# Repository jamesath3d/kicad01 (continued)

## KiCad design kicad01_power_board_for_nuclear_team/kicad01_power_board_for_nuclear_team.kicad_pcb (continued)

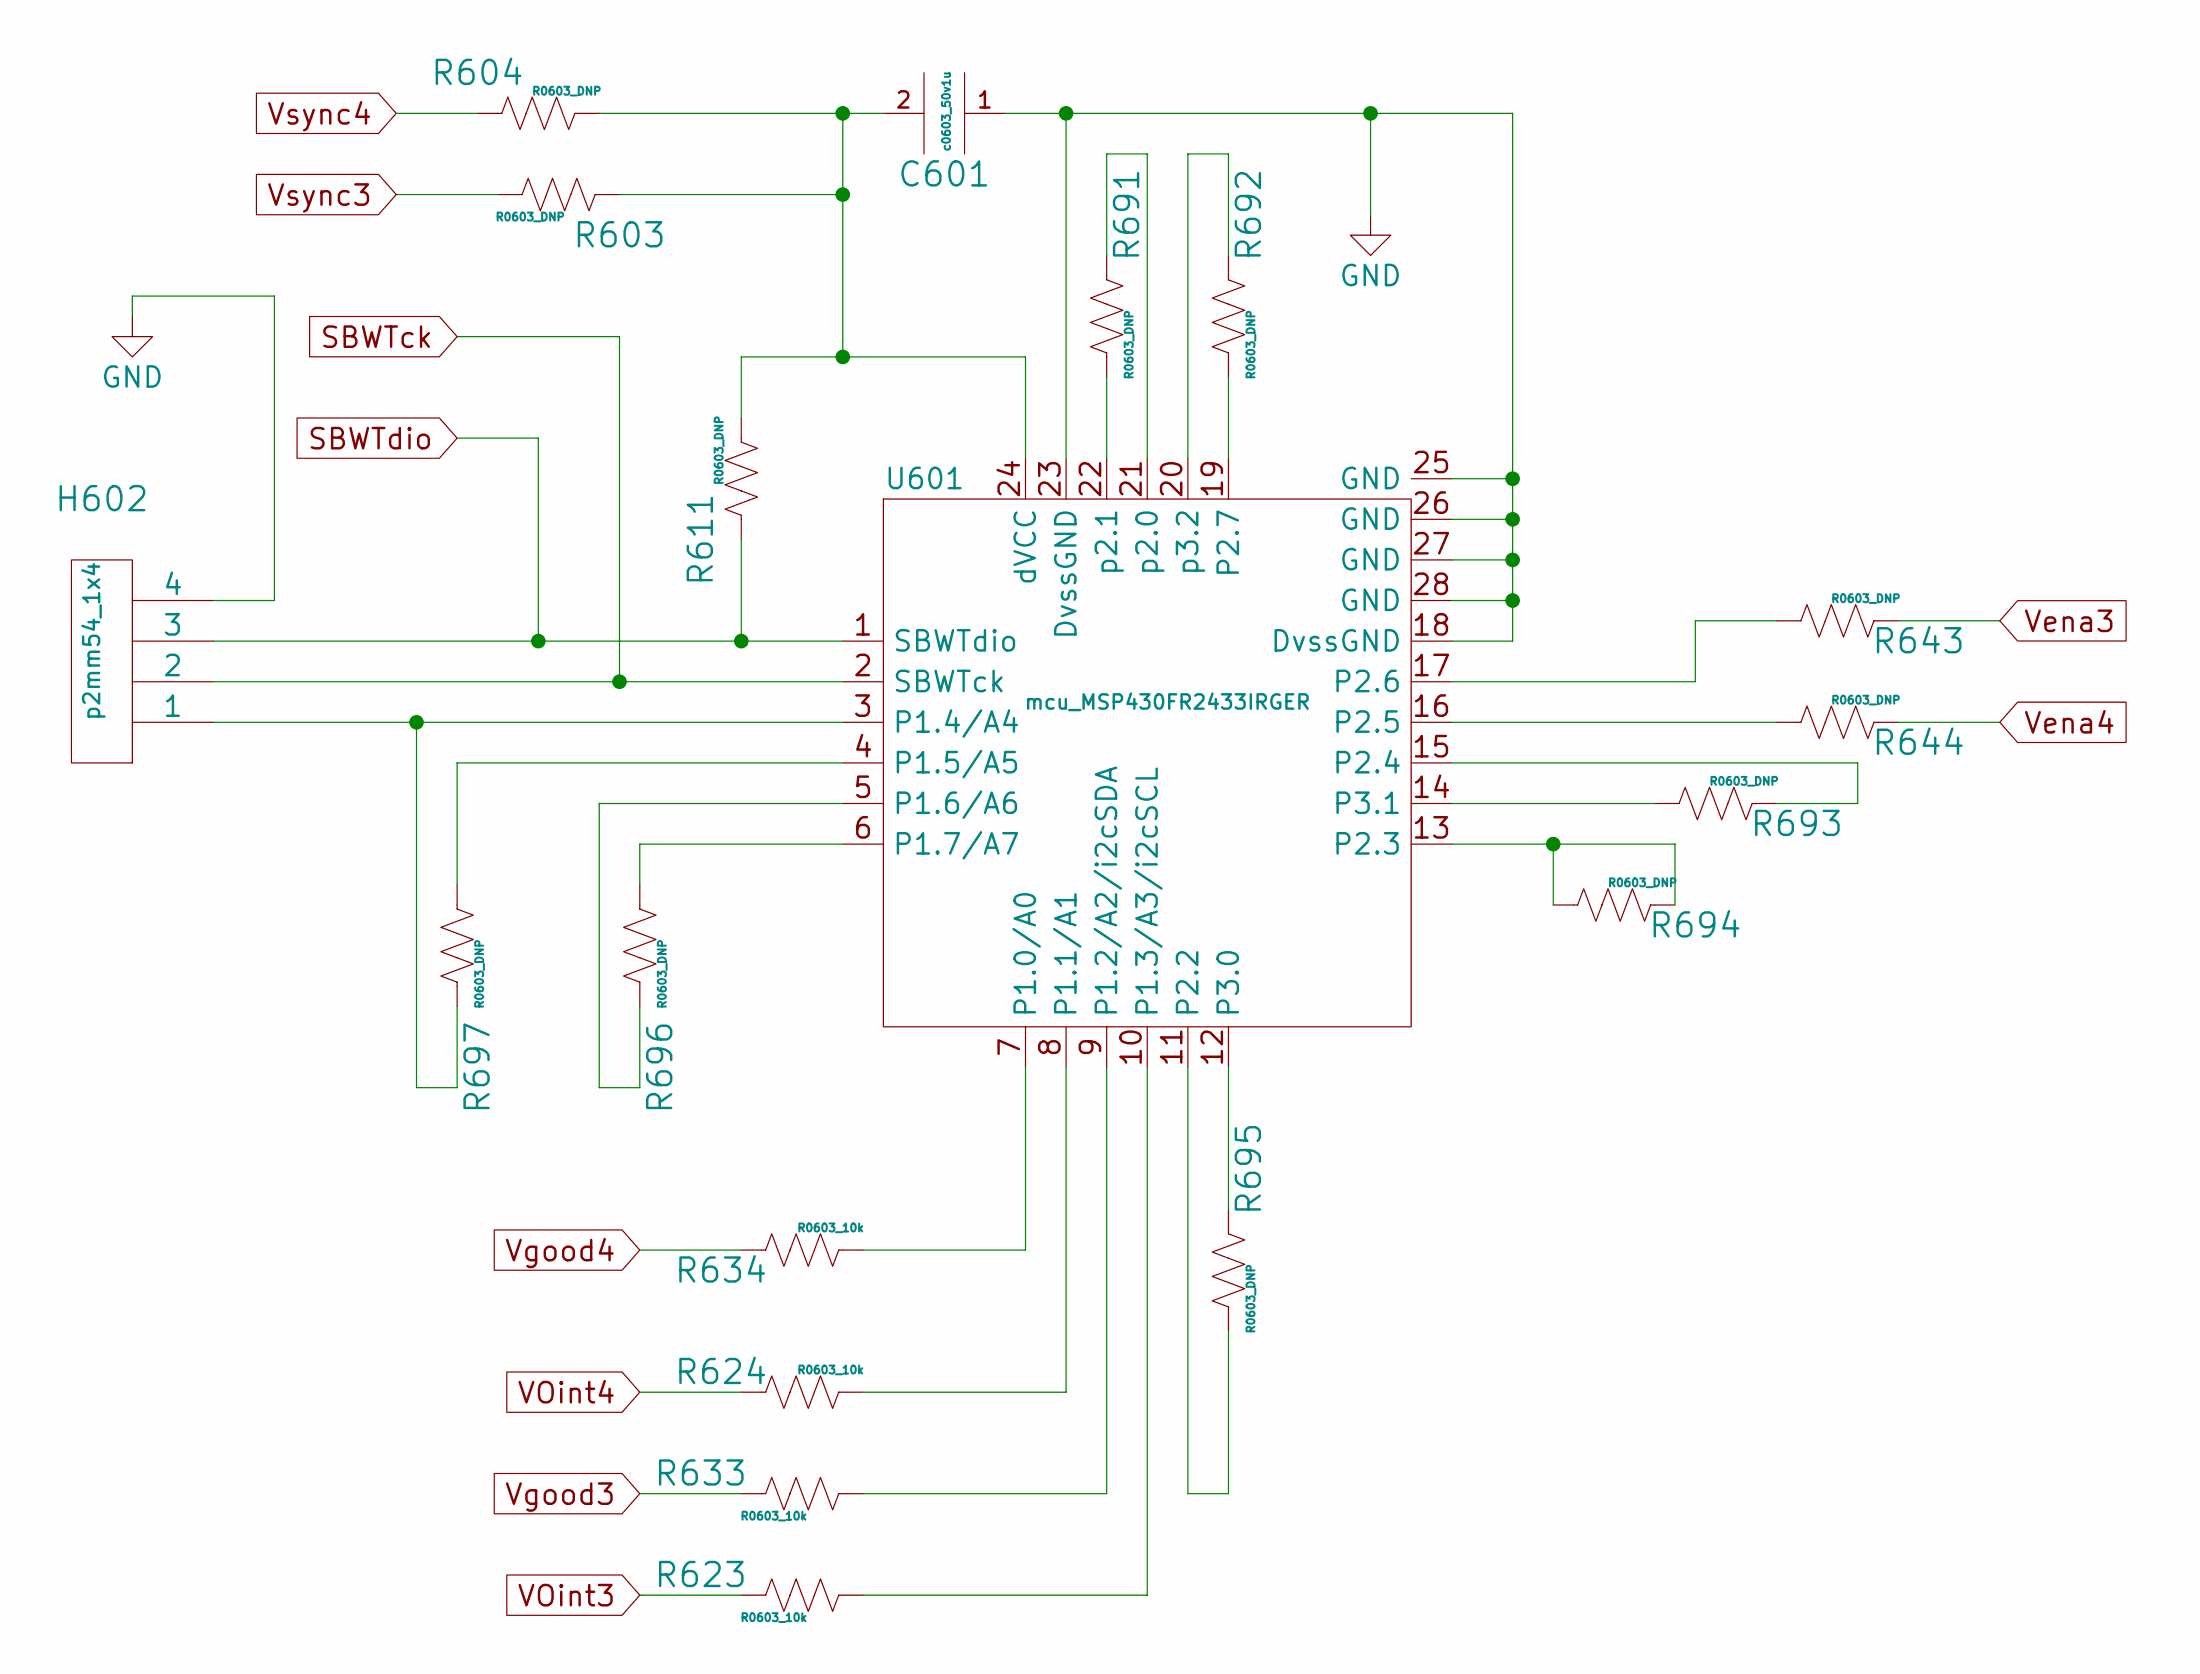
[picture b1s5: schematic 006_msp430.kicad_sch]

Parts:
C601: c0603_50v1u; C0603; PartNum C1608X5R1H105K080AB
H602: p2mm54_1x4; PartNum 3M156515-04-ND
R603, R604, R611, R643, R644, R691, R692, R693, R694, R695, R696, R697: R0603_DNP; R0603; PartNum R0603_DNP
R623, R624, R633, R634: R0603_10k; R0603; PartNum ERJ-PA3F1002V
U601: mcu_MSP430FR2433IRGER; QFN-24-1EP_4x4mm_P0.5mm_EP2.8x2.8mmX; PartNum MSP430FR2433IRGER

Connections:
GND: C601.1, H602.4, U601.18 (DvssGND), U601.23 (DvssGND), U601.25 (GND), U601.26 (GND), U601.27 (GND), U601.28 (GND); also elsewhere on the board
unnamed: C601.2, R603.2, R604.1, R611.1, U601.24 (dVCC)
unnamed: H602.1, R697.1, U601.3 (P1.4/A4)
unnamed: R623.2, U601.10 (P1.3/A3/i2cSCL)
unnamed: R624.1, U601.8 (P1.1/A1)
unnamed: R633.2, U601.9 (P1.2/A2/i2cSDA)
unnamed: R634.1, U601.7 (P1.0/A0)
unnamed: R643.2, U601.17 (P2.6)
unnamed: R644.2, U601.16 (P2.5)
unnamed: R691.1, U601.22 (p2.1)
unnamed: R691.2, U601.21 (p2.0)
unnamed: R692.1, U601.19 (P2.7)
unnamed: R692.2, U601.20 (p3.2)
unnamed: R693.1, U601.15 (P2.4)
unnamed: R693.2, U601.14 (P3.1)
unnamed: R694.1, R694.2, U601.13 (P2.3)
unnamed: R695.1, U601.11 (P2.2)
unnamed: R695.2, U601.12 (P3.0)
unnamed: R696.1, U601.5 (P1.6/A6)
unnamed: R696.2, U601.6 (P1.7/A7)
unnamed: R697.2, U601.4 (P1.5/A5)
SBWTck: H602.2, U601.2 (SBWTck)
SBWTdio: H602.3, R611.2, U601.1 (SBWTdio)
VOint3: R623.1; also elsewhere on the board
VOint4: R624.2; also elsewhere on the board
Vena3: R643.1; also elsewhere on the board
Vena4: R644.1; also elsewhere on the board
Vgood3: R633.1; also elsewhere on the board
Vgood4: R634.2; also elsewhere on the board
Vsync3: R603.1; also elsewhere on the board
Vsync4: R604.2; also elsewhere on the board

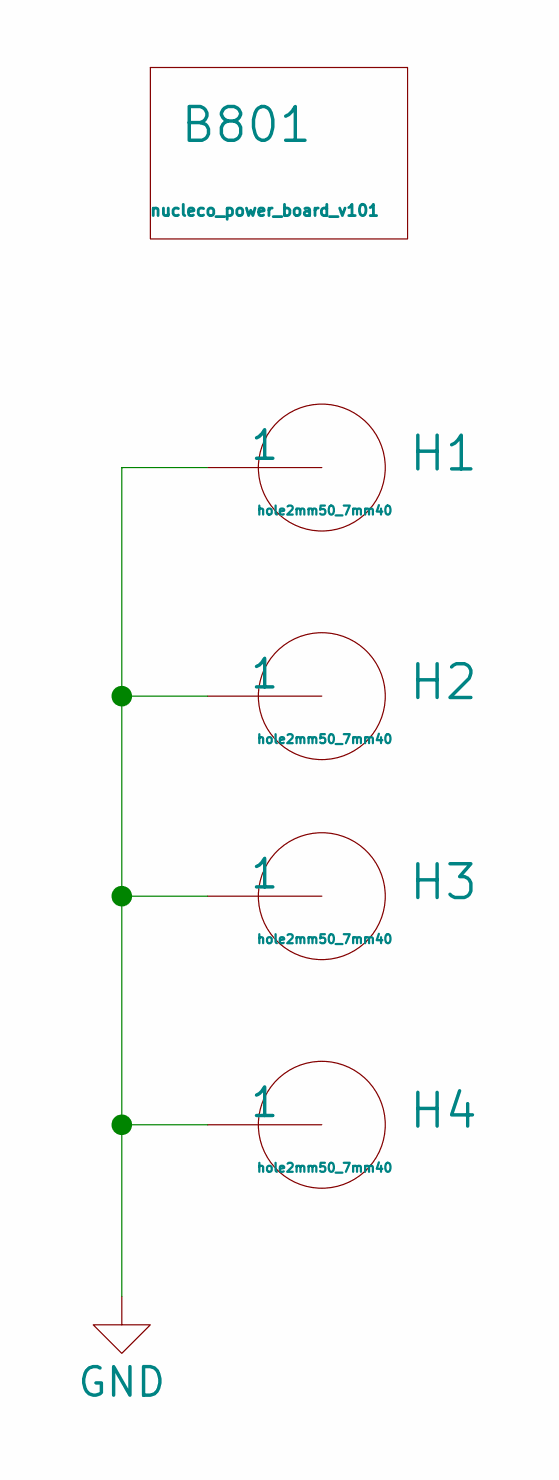
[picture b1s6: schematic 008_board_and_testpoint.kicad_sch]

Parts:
B801: nucleco_power_board_v101; PartNum DNP
H1, H2, H3, H4: hole2mm50_7mm40; PartNum hole2mm50_DNP

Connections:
GND: H1.1, H2.1, H3.1, H4.1; also elsewhere on the board

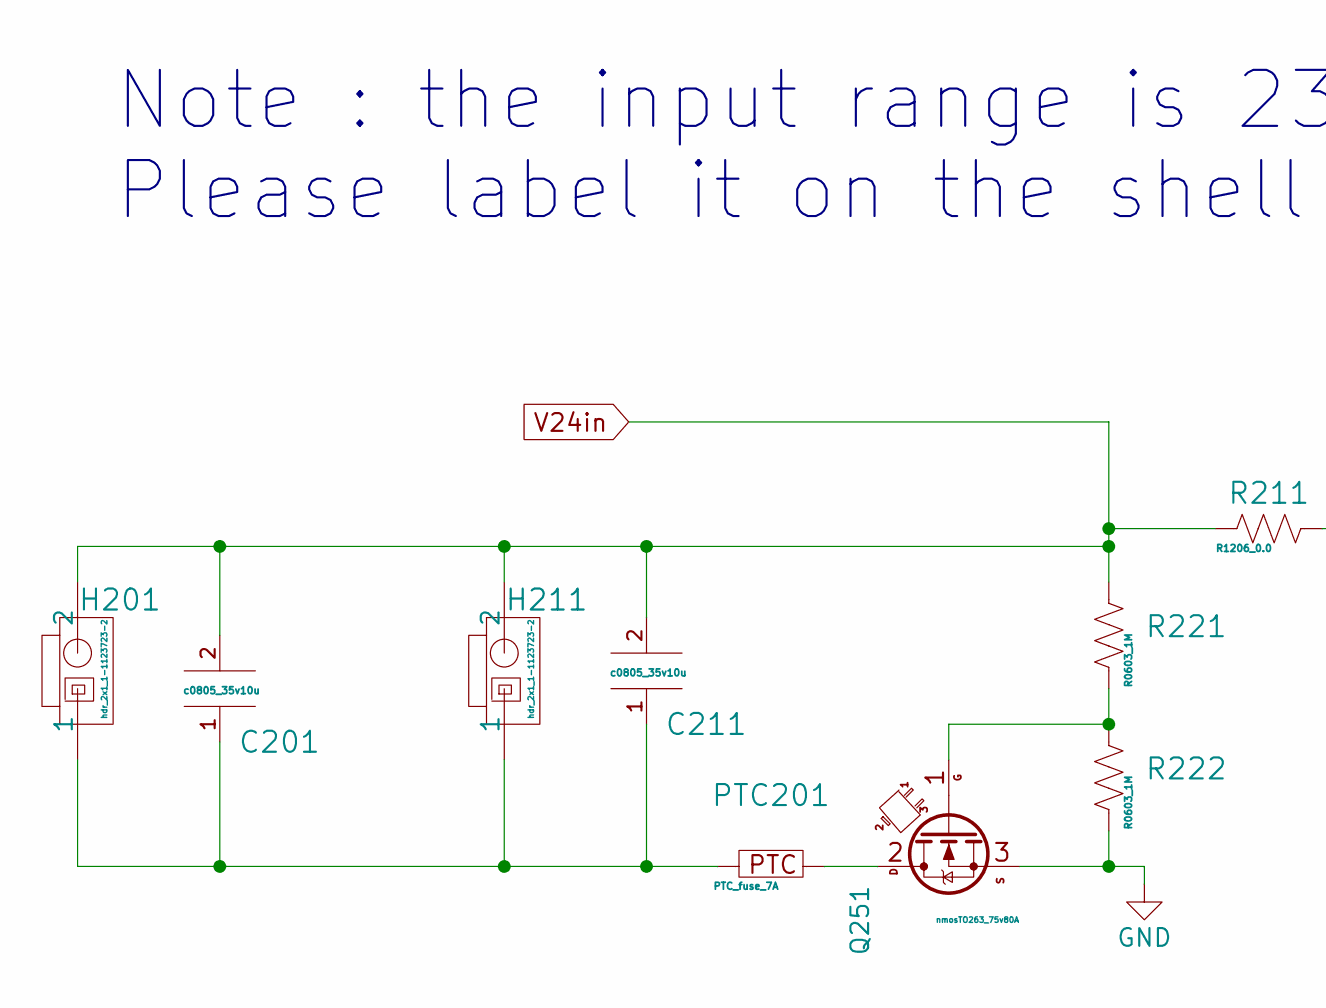
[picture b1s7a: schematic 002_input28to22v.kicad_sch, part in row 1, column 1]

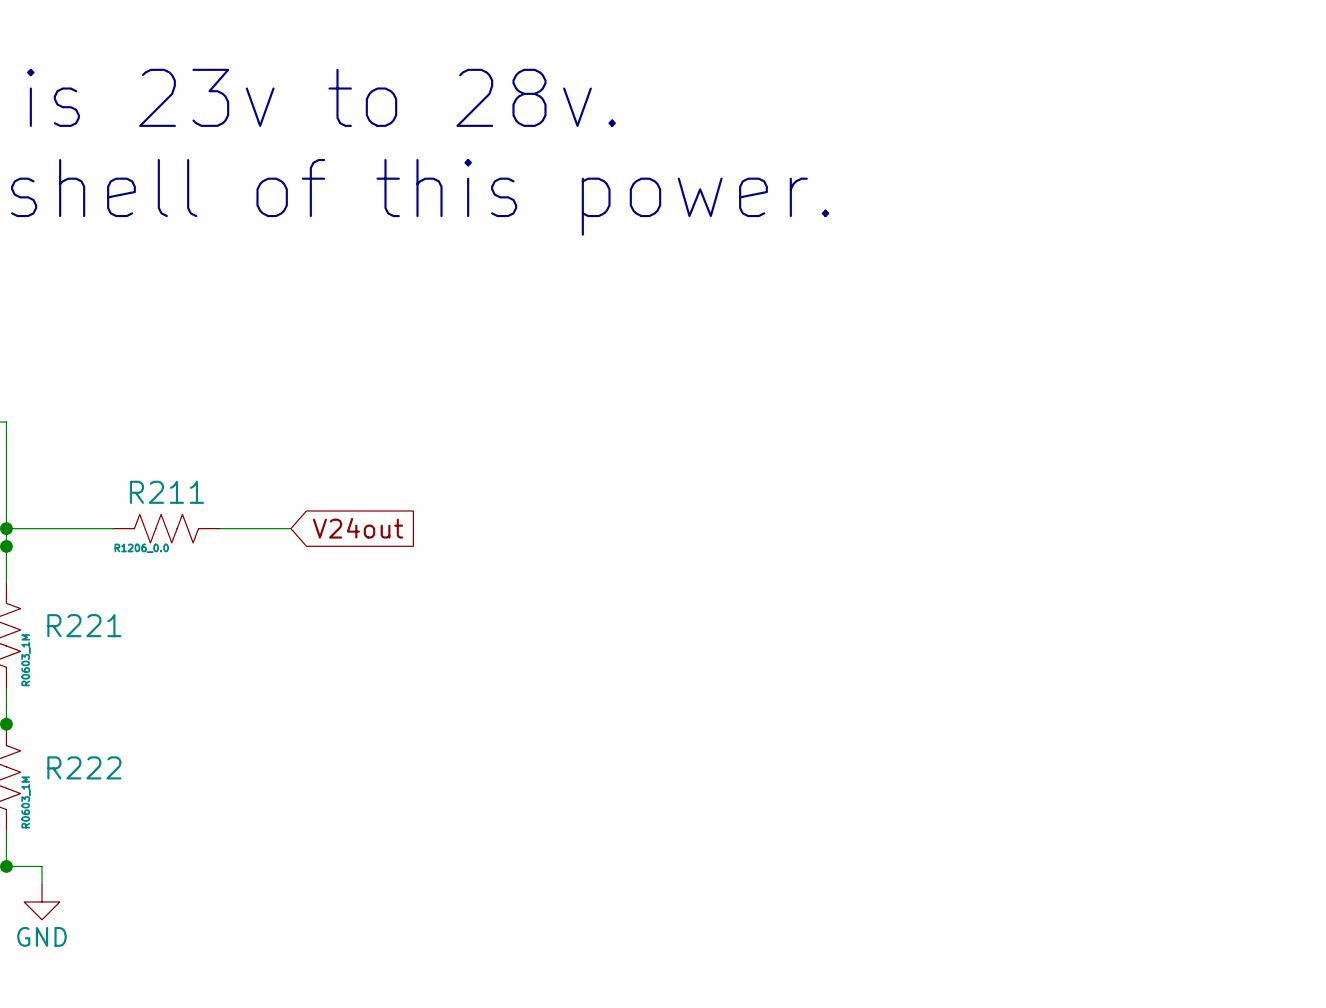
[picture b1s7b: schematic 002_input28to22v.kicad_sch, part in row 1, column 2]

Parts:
C201, C211: c0805_35v10u; C0805mix0603; PartNum C2012X5R1V106M085AC
H201, H211: hdr_2x1_1-1123723-2; PartNum 1-1123723-2
PTC201: PTC_fuse_7A; ptc_fuse_2920; PartNum 2920L700/12MR
Q251: nmosTO263_75v80A; d2pak_TO263; PartNum IRFS3607TRLPBF
R211: R1206_0.0; R1206mix0603; PartNum RC1206FR-070RL
R221, R222: R0603_1M; C0603; PartNum ERJ-U03F1004V

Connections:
GND: Q251.3 (S), R222.1; also elsewhere on the board
unnamed: C201.1, C211.1, H201.1, H211.1, PTC201.1
unnamed: PTC201.2, Q251.2 (D)
unnamed: Q251.1 (G), R221.1, R222.2
V24in: C201.2, C211.2, H201.2, H211.2, R211.1, R221.2; also elsewhere on the board
V24out: R211.2; also elsewhere on the board

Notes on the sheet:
Note : the input range is 23v to 28v. Please label it on the shell of this power.

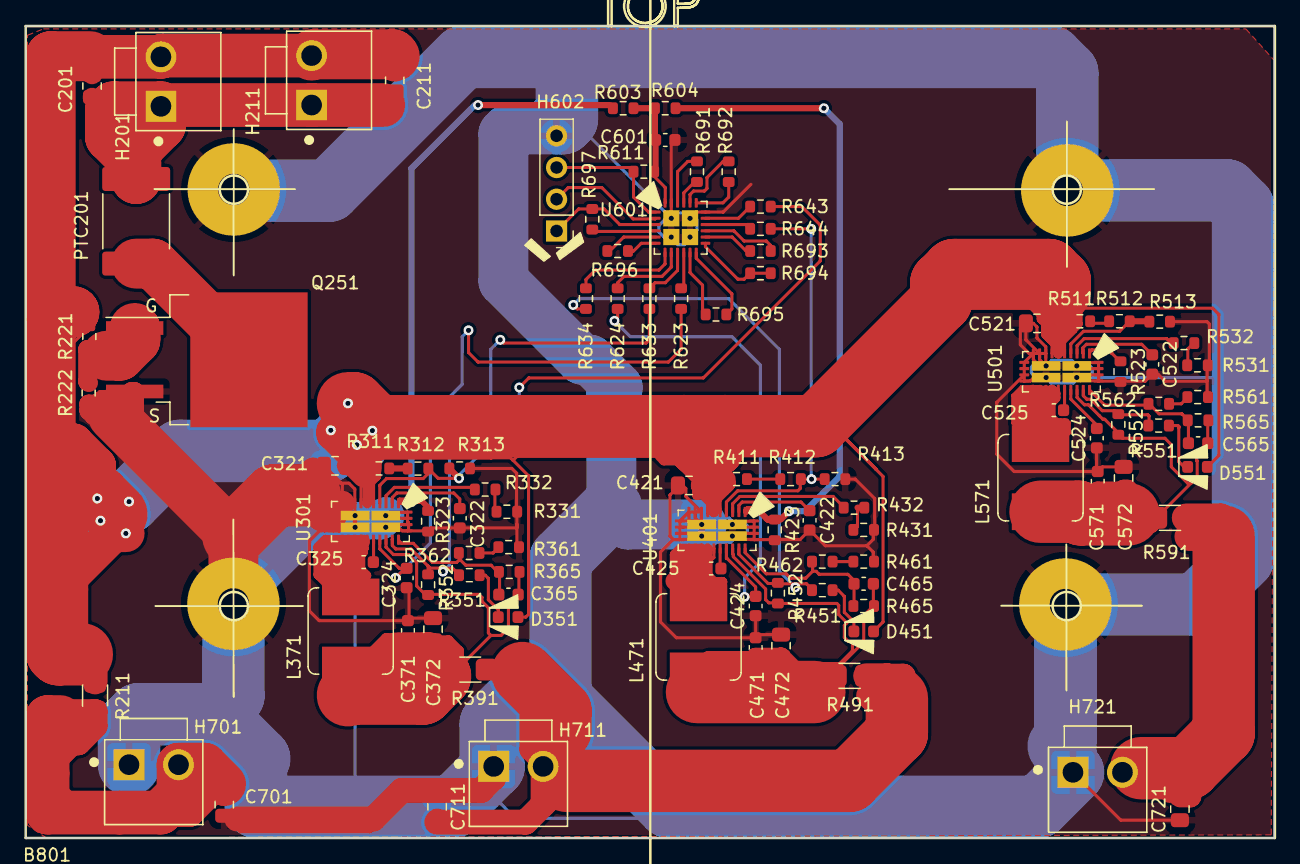
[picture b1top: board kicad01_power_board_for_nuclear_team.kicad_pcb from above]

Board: 2 copper layers, 99.9 x 65.0 mm, 105 parts (0 on the bottom side), 72 nets.
